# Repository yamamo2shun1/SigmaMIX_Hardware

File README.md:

# SigmaMIX
The SigmaMIX is a DSP/BLE board for Turntablist/Portablist, and it's an Open Source Hardware.

# Firmware/Software Repository
* [SigmaMIX Firmware for SiLabs BGM113](https://github.com/tkrworks/SigmaMIX_Firmware)  
* [SigmaMIX Remote App for Android](https://github.com/tkrworks/SigmaMIX_Remote)

**I made sure to be able to control two ADAU1701 from the BGM113 via I2C on June 7 2017!!!**

## Test Video
[Delay Test](https://www.instagram.com/p/BXrRHsZBKkE/)  
[Effect and Scratch DEMO](https://www.instagram.com/p/BXWzQCQBJe1/)  
[Phono and Line inputs Mix and Fader Cutting Test](https://www.instagram.com/p/BV4aKTPhfiU/)  
[3-Band EQ Test via BLE](https://www.instagram.com/p/BVq-pJHB9hm/)  
[Phono EQ Test](https://www.instagram.com/p/BVVsefTBJXY/)  
[Beat and Sine Tone Test](https://www.instagram.com/p/BVFF-J9hF4o/)  
[First Scratch Test](https://www.instagram.com/p/BUi_Y2OhvBm/)  

## SPEC
* DSP: ANALOG DEVICES SigmaDSP [ADAU1701](http://www.analog.com/jp/products/processors-dsp/sigmadsp-audio-processors/adau1701.html) x2
* BLE: Silicon Labs [BGM113](http://jp.silabs.com/products/wireless/bluetooth/bluetooth-low-energy-modules/bgm113-bluetooth-low-energy-module)
* Audio: RCA Input x4 and RCA Output x8
* Power: ONLY 5-16V input [MIC39101](http://www.microchip.com/wwwproducts/en/MIC39100).
* Size: 112.0mm x 59.5mm

## HARDWARE LICENSE
<br /><span xmlns:dct="http://purl.org/dc/terms/" property="dct:title">SigmaMIX</span> by <span xmlns:cc="http://creativecommons.org/ns#" property="cc:attributionName">Shunichi Yamamoto</span> is licensed under a <a rel="license" href="http://creativecommons.org/licenses/by-sa/4.0/">Creative Commons Attribution-ShareAlike 4.0 International License</a>.

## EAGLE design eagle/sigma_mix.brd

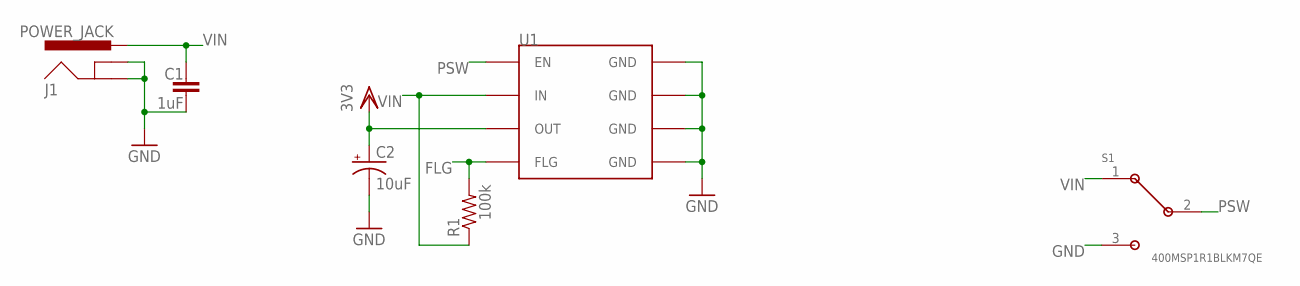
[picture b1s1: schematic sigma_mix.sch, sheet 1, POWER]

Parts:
C1: 1uF; C2012
C2: 10uF; R/2012-12R
J1: POWER_JACK; POWER_JACK_PTH_LOCK
R1: 100k; 0603-RES
S1: 400MSP1R1BLKM7QE
U1: MIC39100; SOIC8

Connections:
FLG: R1.2, U1.4 (FLG)
GND: C1.2, C2.-, J1.GND, J1.GNDBREAK, S1.3, U1.5 (GND), U1.6 (GND), U1.7 (GND), U1.8 (GND); also elsewhere on the board
PSW: S1.2, U1.1 (EN)
VDD: C2.+, U1.3 (OUT); also elsewhere on the board
VIN: C1.1, J1.PWR, R1.1, S1.1, U1.2 (IN)

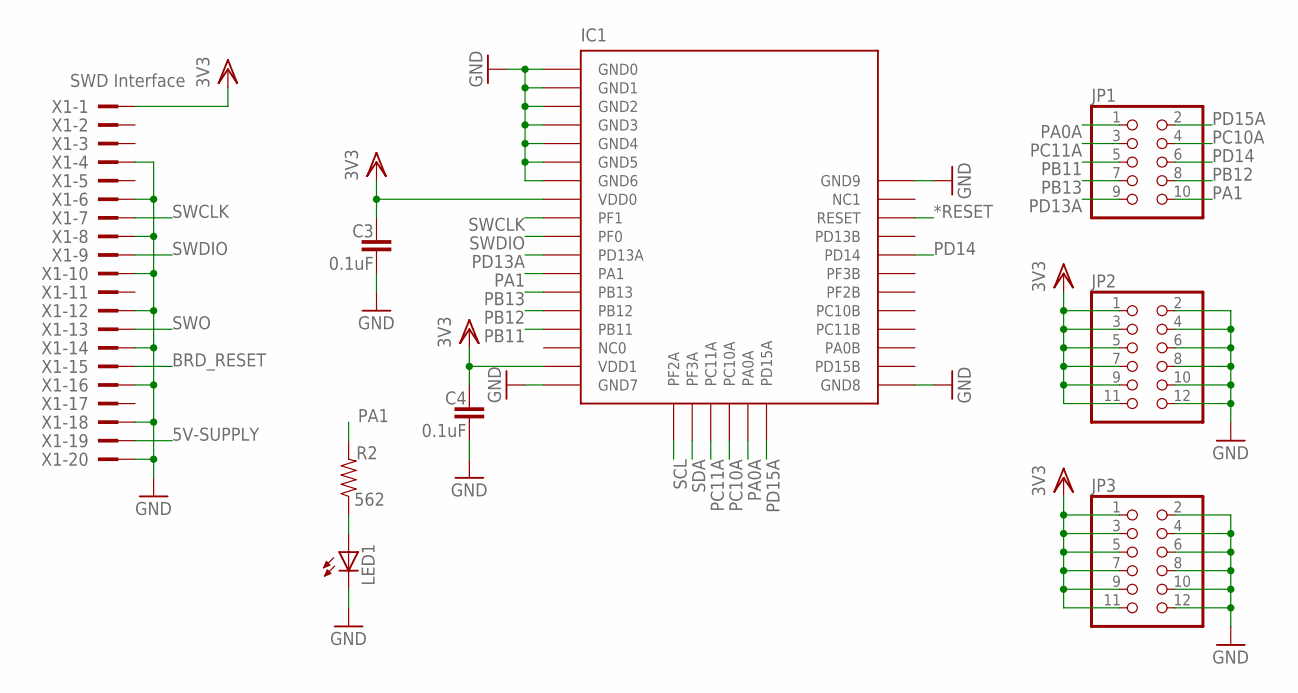
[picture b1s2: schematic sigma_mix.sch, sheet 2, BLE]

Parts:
C3, C4: 0.1uF; C2012
IC1: BGM113; BLE113
JP1: PINHD-2X5; 2X05
JP2, JP3: PINHD-2X6; 2X06
LED1: LEDCHIPLED_1206; CHIPLED_1206
R2: 562; 0603-RES
X1: SWD Interface; PAK100/2500-20

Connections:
5V-SUPPLY: X1.19
*RESET: IC1.P$34 (RESET); also elsewhere on the board
BRD_RESET: X1.15; also elsewhere on the board
GND: C3.2, C4.2, IC1.P$1 (GND0), IC1.P$2 (GND1), IC1.P$3 (GND2), IC1.P$4 (GND3), IC1.P$5 (GND4), IC1.P$6 (GND5), IC1.P$7 (GND6), IC1.P$18 (GND7), IC1.P$25 (GND8), IC1.P$36 (GND9), JP2.2, JP2.4, JP2.6, JP2.8, JP2.10, JP2.12, JP3.2, JP3.4, JP3.6, JP3.8, JP3.10, JP3.12, LED1.C, X1.4, X1.6, X1.8, X1.10, X1.12, X1.14, X1.16, X1.18, X1.20; also elsewhere on the board
unnamed: LED1.A, R2.1
PA0A: IC1.P$23 (PA0A), JP1.1
PA1: IC1.P$12 (PA1), JP1.10, R2.2
PB11: IC1.P$15 (PB11), JP1.5
PB12: IC1.P$14 (PB12), JP1.8
PB13: IC1.P$13 (PB13), JP1.7
PC10A: IC1.P$22 (PC10A), JP1.4
PC11A: IC1.P$21 (PC11A), JP1.3
PD13A: IC1.P$11 (PD13A), JP1.9
PD14: IC1.P$32 (PD14), JP1.6
PD15A: IC1.P$24 (PD15A), JP1.2
SCL: IC1.P$19 (PF2A); also elsewhere on the board
SDA: IC1.P$20 (PF3A); also elsewhere on the board
SWCLK: IC1.P$9 (PF1), X1.7
SWDIO: IC1.P$10 (PF0), X1.9
SWO: X1.13
VDD: C3.1, C4.1, IC1.P$8 (VDD0), IC1.P$17 (VDD1), JP2.1, JP2.3, JP2.5, JP2.7, JP2.9, JP2.11, JP3.1, JP3.3, JP3.5, JP3.7, JP3.9, JP3.11, X1.1; also elsewhere on the board

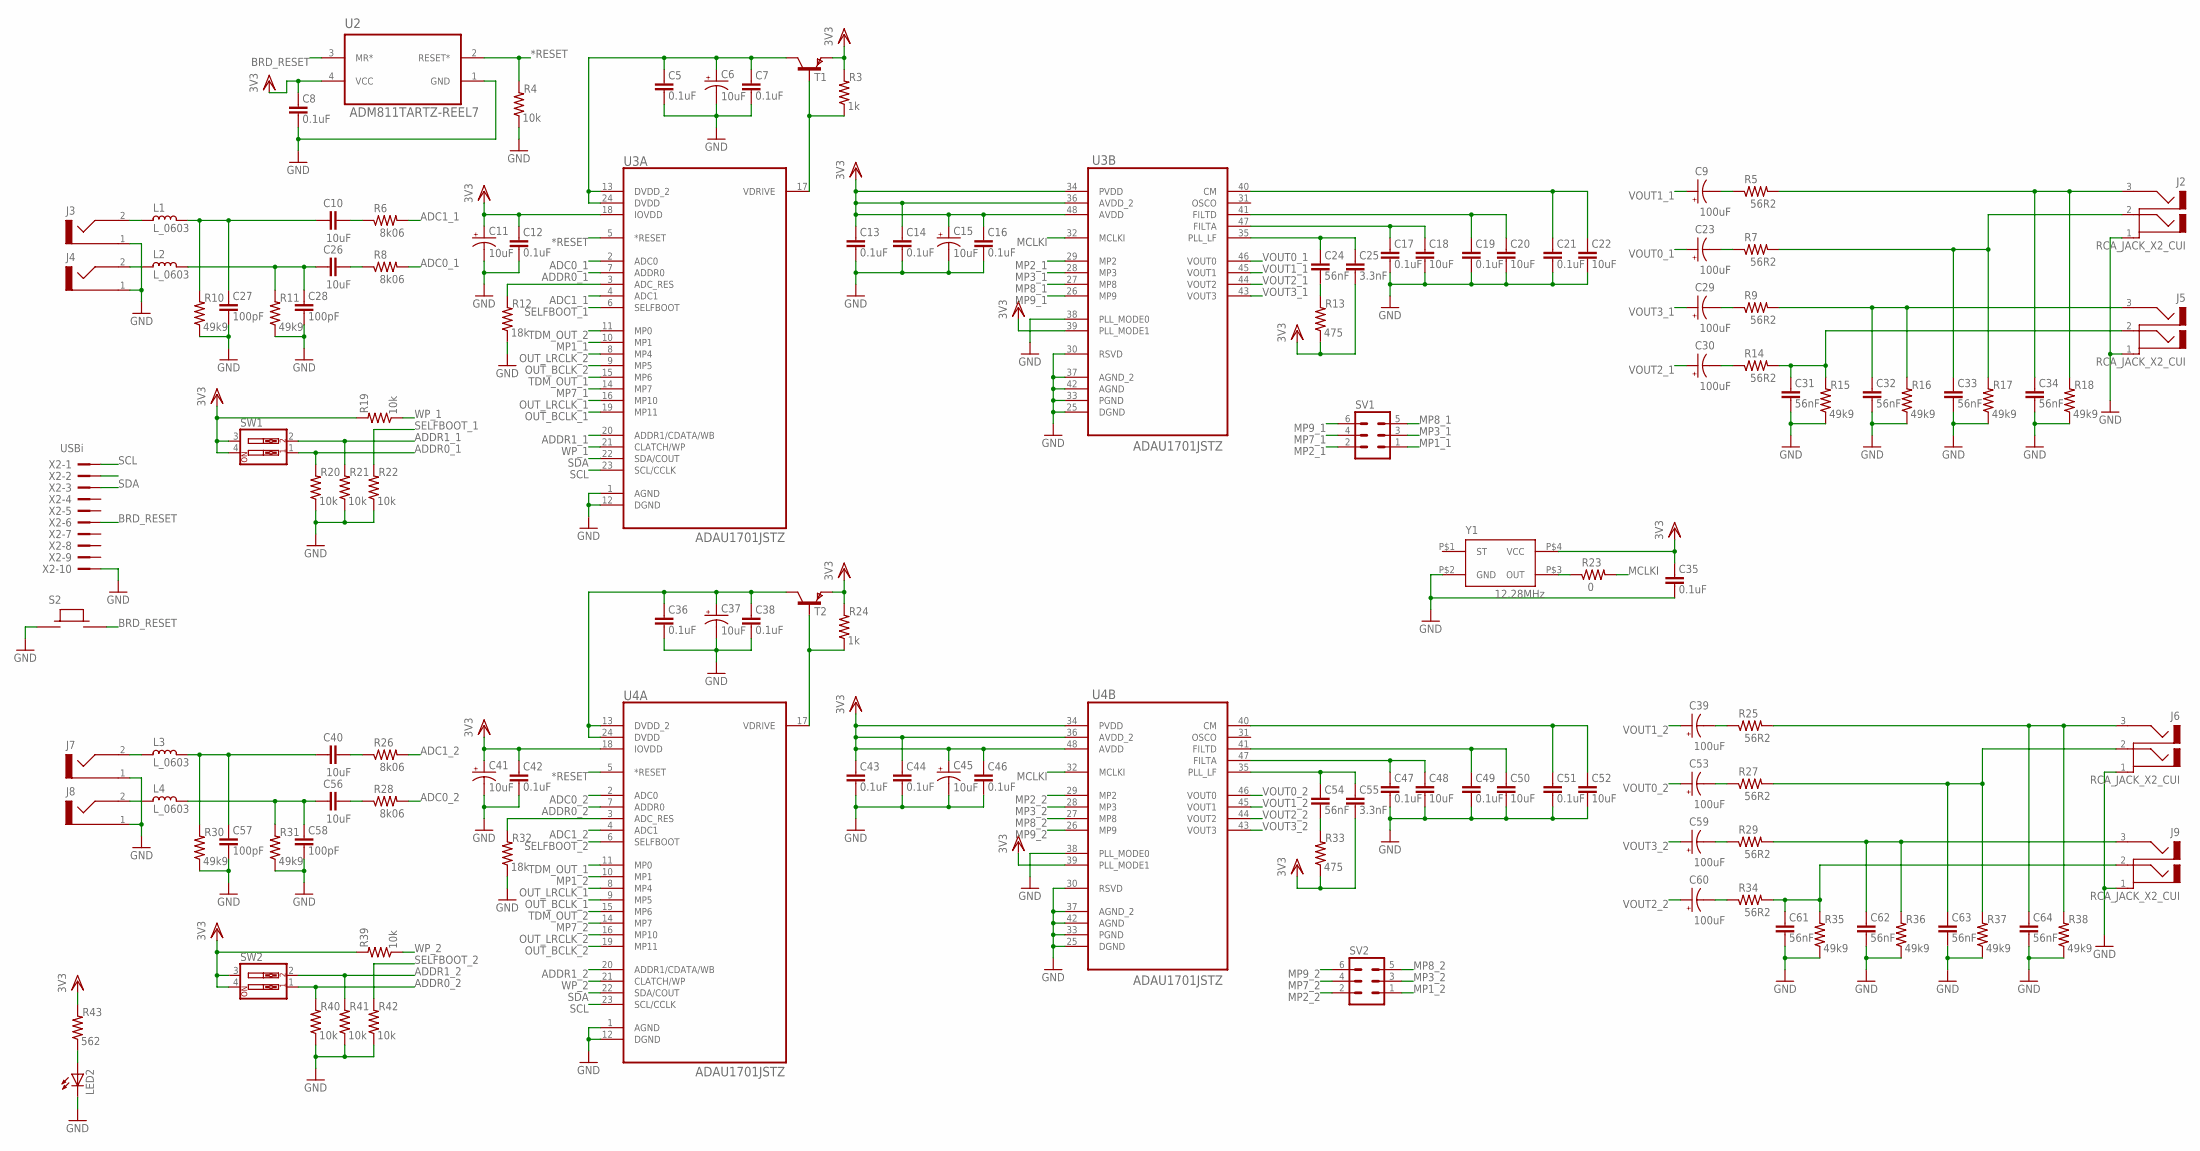
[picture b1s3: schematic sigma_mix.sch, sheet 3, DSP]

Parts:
C5, C7, C8, C12, C13, C14, C16, C17, C19, C21, C35, C36, C38, C42, C43, C44, C46, C47, C49, C51: 0.1uF; C2012
C6, C11, C15, C37, C41, C45: 10uF; R/2012-12R
C9, C23, C29, C30, C39, C53, C59, C60: 100uF; B/3528-21R
C10, C18, C20, C22, C26, C40, C48, C50, C52, C56: 10uF; C2012
C24, C31, C32, C33, C34, C54, C61, C62, C63, C64: 56nF; C2012
C25, C55: 3.3nF; C2012
C27, C28, C57, C58: 100pF; C2012
J2, J5, J6, J9: RCA_JACK_X2_CUI
J3, J4, J7, J8: RCA_JACK_CUI
L1, L2, L3, L4: L_0603; L0603
LED2: LEDCHIPLED_1206; CHIPLED_1206
R3, R24: 1k; 0603-RES
R4, R19, R20, R21, R22, R39, R40, R41, R42: 10k; 0603-RES
R5, R7, R9, R14, R25, R27, R29, R34: 56R2; 0603-RES
R6, R8, R26, R28: 8k06; 0603-RES
R10, R11, R15, R16, R17, R18, R30, R31, R35, R36, R37, R38: 49k9; 0603-RES
R12, R32: 18k; 0603-RES
R13, R33: 475; 0603-RES
R23: 0; 0603-RES
R43: 562; 0603-RES
S2: OMRON_B3M
SV1, SV2: MA03-2
SW1, SW2: SW_DIP-2; EDG-02
T1, T2: PNPSOT23; SOT-23
U2: ADM811TARTZ-REEL7; SOT143P290X130-4N
U3, U4: ADAU1701JSTZ; QFP50P900X900X160-48N
X2: USBi; PAK100/2500-10
Y1: 12.28MHz; SG-210

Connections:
*RESET: R4.2, U2.2 (RESET*), U3.5 (*RESET), U4.5 (*RESET); also elsewhere on the board
ADC0_1: R8.2, U3.2 (ADC0)
ADC0_2: R28.2, U4.2 (ADC0)
ADC1_1: R6.2, U3.4 (ADC1)
ADC1_2: R26.2, U4.4 (ADC1)
ADDR0_1: R20.2, SW1.1, U3.7 (ADDR0)
ADDR0_2: R40.2, SW2.1, U4.7 (ADDR0)
ADDR1_1: R21.2, SW1.2, U3.20 (ADDR1/CDATA/WB)
ADDR1_2: R41.2, SW2.2, U4.20 (ADDR1/CDATA/WB)
BRD_RESET: S2.P$2, U2.3 (MR*), X2.6; also elsewhere on the board
DVDD: C5.1, C6.+, C7.1, T1.1 (C), U3.13 (DVDD_2), U3.24 (DVDD)
GND: C5.2, C6.-, C7.2, C8.2, C11.-, C12.2, C13.2, C14.2, C15.-, C16.2, C17.2, C18.2, C19.2, C20.2, C21.2, C22.2, C27.2, C28.2, C31.2, C32.2, C33.2, C34.2, C35.2, C36.2, C37.-, C38.2, C41.-, C42.2, C43.2, C44.2, C45.-, C46.2, C47.2, C48.2, C49.2, C50.2, C51.2, C52.2, C57.2, C58.2, C61.2, C62.2, C63.2, C64.2, J2.1, J3.1, J4.1, J5.1, J6.1, J7.1, J8.1, J9.1, LED2.C, R4.1, R10.1, R11.1, R12.1, R15.1, R16.1, R17.1, R18.1, R20.1, R21.1, R22.1, R30.1, R31.1, R32.1, R35.1, R36.1, R37.1, R38.1, R40.1, R41.1, R42.1, S2.P$1, U2.1 (GND), U3.1 (AGND), U3.12 (DGND), U3.25 (DGND), U3.30 (RSVD), U3.33 (PGND), U3.37 (AGND_2), U3.38 (PLL_MODE0), U3.42 (AGND), U4.1 (AGND), U4.12 (DGND), U4.25 (DGND), U4.30 (RSVD), U4.33 (PGND), U4.37 (AGND_2), U4.38 (PLL_MODE0), U4.42 (AGND), X2.10, Y1.P$2 (GND); also elsewhere on the board
MCLKI: R23.2, U3.32 (MCLKI), U4.32 (MCLKI)
MP1_1: SV1.1, U3.10 (MP1)
MP1_2: SV2.1, U4.10 (MP1)
MP2_1: SV1.2, U3.29 (MP2)
MP2_2: SV2.2, U4.29 (MP2)
MP3_1: SV1.3, U3.28 (MP3)
MP3_2: SV2.3, U4.28 (MP3)
MP7_1: SV1.4, U3.14 (MP7)
MP7_2: SV2.4, U4.14 (MP7)
MP8_1: SV1.5, U3.27 (MP8)
MP8_2: SV2.5, U4.27 (MP8)
MP9_1: SV1.6, U3.26 (MP9)
MP9_2: SV2.6, U4.26 (MP9)
unnamed: R3.1, T1.3 (B), U3.17 (VDRIVE)
unnamed: C24.2, R13.2
unnamed: C24.1, C25.1, U3.35 (PLL_LF)
unnamed: C17.1, C18.1, U3.47 (FILTA)
unnamed: R23.1, Y1.P$3 (OUT)
unnamed: C19.1, C20.1, U3.41 (FILTD)
unnamed: C21.1, C22.1, U3.40 (CM)
unnamed: R12.2, U3.3 (ADC_RES)
unnamed: LED2.A, R43.1
unnamed: C10.2, C27.1, L1.1, R10.2
unnamed: C10.1, R6.1
unnamed: C26.2, C28.1, L2.1, R11.2
unnamed: C26.1, R8.1
unnamed: C9.-, R5.1
unnamed: J3.2, L1.2
unnamed: C23.-, R7.1
unnamed: C29.-, R9.1
unnamed: C30.-, R14.1
unnamed: C31.1, J5.2, R14.2, R15.2
unnamed: C32.1, J5.3, R9.2, R16.2
unnamed: C33.1, J2.2, R7.2, R17.2
unnamed: C34.1, J2.3, R5.2, R18.2
unnamed: J4.2, L2.2
unnamed: R24.1, T2.3 (B), U4.17 (VDRIVE)
unnamed: C36.1, C37.+, C38.1, T2.1 (C), U4.13 (DVDD_2), U4.24 (DVDD)
unnamed: C54.2, R33.2
unnamed: C54.1, C55.1, U4.35 (PLL_LF)
unnamed: C47.1, C48.1, U4.47 (FILTA)
unnamed: C49.1, C50.1, U4.41 (FILTD)
unnamed: C51.1, C52.1, U4.40 (CM)
unnamed: R32.2, U4.3 (ADC_RES)
unnamed: C40.2, C57.1, L3.1, R30.2
unnamed: C40.1, R26.1
unnamed: C56.2, C58.1, L4.1, R31.2
unnamed: C56.1, R28.1
unnamed: C39.-, R25.1
unnamed: C53.-, R27.1
unnamed: C59.-, R29.1
unnamed: C60.-, R34.1
unnamed: C61.1, J9.2, R34.2, R35.2
unnamed: C62.1, J9.3, R29.2, R36.2
unnamed: C63.1, J6.2, R27.2, R37.2
unnamed: C64.1, J6.3, R25.2, R38.2
unnamed: J7.2, L3.2
unnamed: J8.2, L4.2
OUT_BCLK_1: U3.19 (MP11), U4.9 (MP5)
OUT_BCLK_2: U3.9 (MP5), U4.19 (MP11)
OUT_LRCLK_1: U3.16 (MP10), U4.8 (MP4)
OUT_LRCLK_2: U3.8 (MP4), U4.16 (MP10)
SCL: U3.23 (SCL/CCLK), U4.23 (SCL/CCLK), X2.1; also elsewhere on the board
SDA: U3.22 (SDA/COUT), U4.22 (SDA/COUT), X2.3; also elsewhere on the board
SELFBOOT_1: R22.2, U3.6 (SELFBOOT)
SELFBOOT_2: R42.2, U4.6 (SELFBOOT)
TDM_OUT_1: U3.15 (MP6), U4.11 (MP0)
TDM_OUT_2: U3.11 (MP0), U4.15 (MP6)
VDD: C8.1, C11.+, C12.1, C13.1, C14.1, C15.+, C16.1, C25.2, C35.1, C41.+, C42.1, C43.1, C44.1, C45.+, C46.1, C55.2, R3.2, R13.1, R19.2, R24.2, R33.1, R39.2, R43.2, SW1.3, SW1.4, SW2.3, SW2.4, T1.2 (E), T2.2 (E), U2.4 (VCC), U3.18 (IOVDD), U3.34 (PVDD), U3.36 (AVDD_2), U3.39 (PLL_MODE1), U3.48 (AVDD), U4.18 (IOVDD), U4.34 (PVDD), U4.36 (AVDD_2), U4.39 (PLL_MODE1), U4.48 (AVDD), Y1.P$4 (VCC); also elsewhere on the board
VOUT0_1: C23.+, U3.46 (VOUT0)
VOUT0_2: C53.+, U4.46 (VOUT0)
VOUT1_1: C9.+, U3.45 (VOUT1)
VOUT1_2: C39.+, U4.45 (VOUT1)
VOUT2_1: C30.+, U3.44 (VOUT2)
VOUT2_2: C60.+, U4.44 (VOUT2)
VOUT3_1: C29.+, U3.43 (VOUT3)
VOUT3_2: C59.+, U4.43 (VOUT3)
WP_1: R19.1, U3.21 (CLATCH/WP)
WP_2: R39.1, U4.21 (CLATCH/WP)

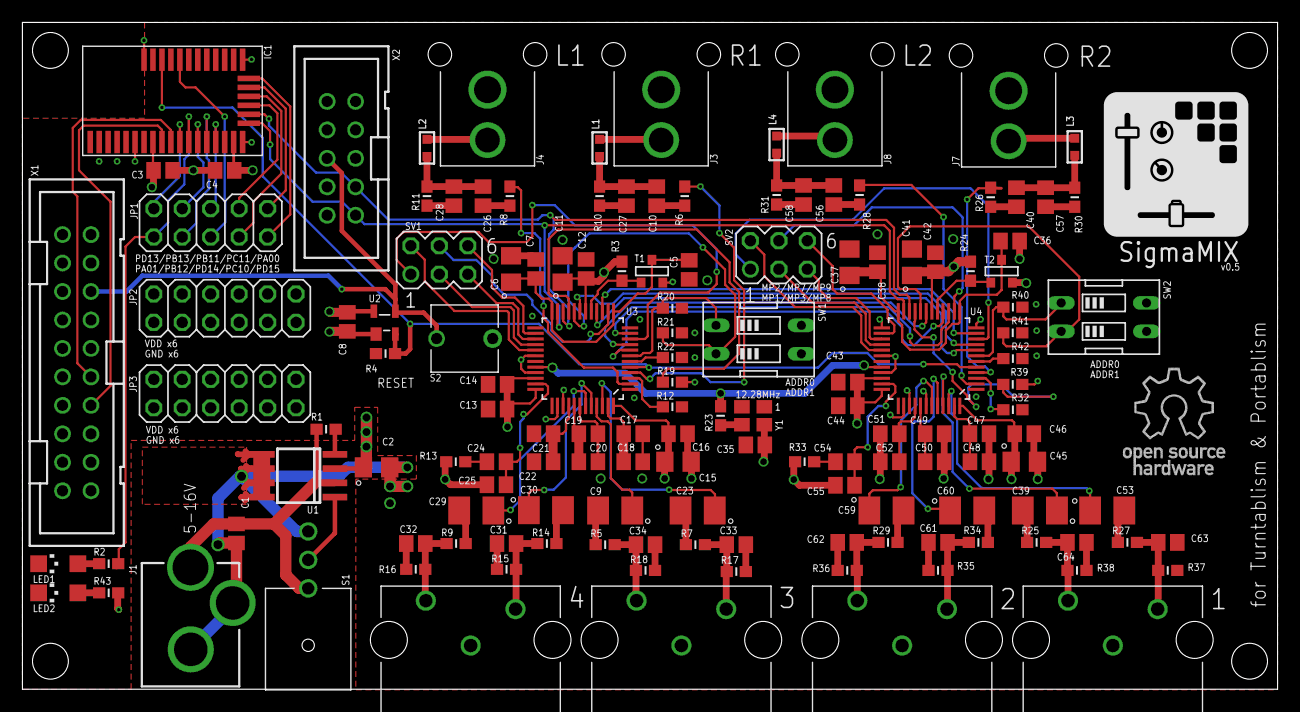
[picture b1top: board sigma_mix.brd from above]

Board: 4 copper layers, 112.0 x 59.5 mm, 141 parts (0 on the bottom side), 107 nets.

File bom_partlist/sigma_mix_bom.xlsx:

Part | Value | Package | Description | Digikey
C1 | 1uF | 2012 | Multilayer Ceramic Capacitor | 490-1691-1-ND
C2 | 10uF | 2012 | Tantalum Capacitor | 478-8115-1-ND
C3 | 0.1uF | 2012 | Multilayer Ceramic Capacitor | 490-1683-6-ND
C4 | 0.1uF | 2012 | Multilayer Ceramic Capacitor | 490-1683-6-ND
C5 | 0.1uF | 2012 | Multilayer Ceramic Capacitor | 490-1683-6-ND
C6 | 10uF | 2012 | Tantalum Capacitor | 478-8115-1-ND
C7 | 0.1uF | 2012 | Multilayer Ceramic Capacitor | 490-1683-6-ND
C8 | 0.1uF | 2012 | Multilayer Ceramic Capacitor | 490-1683-6-ND
C9 | 100uF | 3528 | Tantalum Capacitor | 718-1313-1-ND
C10 | 10uF | 2012 | Multilayer Ceramic Capacitor | 490-3905-1-ND
C11 | 10uF | 2012 | Tantalum Capacitor | 478-8115-1-ND
C12 | 0.1uF | 2012 | Multilayer Ceramic Capacitor | 490-1683-6-ND
C13 | 0.1uF | 2012 | Multilayer Ceramic Capacitor | 490-1683-6-ND
C14 | 0.1uF | 2012 | Multilayer Ceramic Capacitor | 490-1683-6-ND
C15 | 10uF | 2012 | Tantalum Capacitor | 478-8115-1-ND
C16 | 0.1uF | 2012 | Multilayer Ceramic Capacitor | 490-1683-6-ND
C17 | 0.1uF | 2012 | Multilayer Ceramic Capacitor | 490-1683-6-ND
C18 | 10uF | 2012 | Multilayer Ceramic Capacitor | 490-3905-1-ND
C19 | 0.1uF | 2012 | Multilayer Ceramic Capacitor | 490-1683-6-ND
C20 | 10uF | 2012 | Multilayer Ceramic Capacitor | 490-3905-1-ND
C21 | 0.1uF | 2012 | Multilayer Ceramic Capacitor | 490-1683-6-ND
C22 | 10uF | 2012 | Multilayer Ceramic Capacitor | 490-3905-1-ND
C23 | 100uF | 3528 | Tantalum Capacitor | 718-1313-1-ND
C24 | 56nF | 2012 | Multilayer Ceramic Capacitor | 490-1662-1-ND
C25 | 3.3nF | 2012 | Multilayer Ceramic Capacitor | 399-1153-1-ND
C26 | 10uF | 2012 | Multilayer Ceramic Capacitor | 490-3905-1-ND
C27 | 100pF | 2012 | Multilayer Ceramic Capacitor | 490-1615-1-ND
C28 | 100pF | 2012 | Multilayer Ceramic Capacitor | 490-1615-1-ND
C29 | 100uF | 3528 | Tantalum Capacitor | 718-1313-1-ND
C30 | 100uF | 3528 | Tantalum Capacitor | 718-1313-1-ND
C31 | 56nF | 2012 | Multilayer Ceramic Capacitor | 490-1662-1-ND
C32 | 56nF | 2012 | Multilayer Ceramic Capacitor | 490-1662-1-ND
C33 | 56nF | 2012 | Multilayer Ceramic Capacitor | 490-1662-1-ND
C34 | 56nF | 2012 | Multilayer Ceramic Capacitor | 490-1662-1-ND
C35 | 0.1uF | 2012 | Multilayer Ceramic Capacitor | 490-1683-6-ND
C36 | 0.1uF | 2012 | Multilayer Ceramic Capacitor | 490-1683-6-ND
C37 | 10uF | 2012 | Tantalum Capacitor | 478-8115-1-ND
C38 | 0.1uF | 2012 | Multilayer Ceramic Capacitor | 490-1683-6-ND
C39 | 100uF | 3528 | Tantalum Capacitor | 718-1313-1-ND
C40 | 10uF | 2012 | Multilayer Ceramic Capacitor | 490-3905-1-ND
C41 | 10uF | 2012 | Tantalum Capacitor | 478-8115-1-ND
C42 | 0.1uF | 2012 | Multilayer Ceramic Capacitor | 490-1683-6-ND
C43 | 0.1uF | 2012 | Multilayer Ceramic Capacitor | 490-1683-6-ND
C44 | 0.1uF | 2012 | Multilayer Ceramic Capacitor | 490-1683-6-ND
C45 | 10uF | 2012 | Tantalum Capacitor | 478-8115-1-ND
C46 | 0.1uF | 2012 | Multilayer Ceramic Capacitor | 490-1683-6-ND
C47 | 0.1uF | 2012 | Multilayer Ceramic Capacitor | 490-1683-6-ND
C48 | 10uF | 2012 | Multilayer Ceramic Capacitor | 490-3905-1-ND
C49 | 0.1uF | 2012 | Multilayer Ceramic Capacitor | 490-1683-6-ND
C50 | 10uF | 2012 | Multilayer Ceramic Capacitor | 490-3905-1-ND
C51 | 0.1uF | 2012 | Multilayer Ceramic Capacitor | 490-1683-6-ND
C52 | 10uF | 2012 | Multilayer Ceramic Capacitor | 490-3905-1-ND
C53 | 100uF | 3528 | Tantalum Capacitor | 718-1313-1-ND
C54 | 56nF | 2012 | Multilayer Ceramic Capacitor | 490-1662-1-ND
C55 | 3.3nF | 2012 | Multilayer Ceramic Capacitor | 399-1153-1-ND
C56 | 10uF | 2012 | Multilayer Ceramic Capacitor | 490-3905-1-ND
C57 | 100pF | 2012 | Multilayer Ceramic Capacitor | 490-1615-1-ND
C58 | 100pF | 2012 | Multilayer Ceramic Capacitor | 490-1615-1-ND
C59 | 100uF | 3528 | Tantalum Capacitor | 718-1313-1-ND
C60 | 100uF | 3528 | Tantalum Capacitor | 718-1313-1-ND
C61 | 56nF | 2012 | Multilayer Ceramic Capacitor | 490-1662-1-ND
C62 | 56nF | 2012 | Multilayer Ceramic Capacitor | 490-1662-1-ND
C63 | 56nF | 2012 | Multilayer Ceramic Capacitor | 490-1662-1-ND
C64 | 56nF | 2012 | Multilayer Ceramic Capacitor | 490-1662-1-ND
IC1 | BGM113 | LGA Module | Bluetooth Module | 336-3817-1-ND
J1 | DC_JACK | Through Hole | Power Connector |  | 未実装ミジッソウ
J2 | RCA2_JACK | Through Hole | Audio Connector | CP-1435-ND | 未実装ミジッソウ
J3 | RCA_JACK | Through Hole | Audio Connector | CP-1419-ND | 未実装ミジッソウ
J4 | RCA_JACK | Through Hole | Audio Connector | CP-1420-ND | 未実装ミジッソウ
J5 | RCA2_JACK | Through Hole | Audio Connector | CP-1435-ND | 未実装ミジッソウ
J6 | RCA2_JACK | Through Hole | Audio Connector | CP-1435-ND | 未実装ミジッソウ
J7 | RCA_JACK | Through Hole | Audio Connector | CP-1419-ND | 未実装ミジッソウ
J8 | RCA_JACK | Through Hole | Audio Connector | CP-1420-ND | 未実装ミジッソウ
J9 | RCA2_JACK | Through Hole | Audio Connector | CP-1435-ND | 未実装ミジッソウ
JP1 | 2x5 | Through Hole | Pin Header |  | 未実装ミジッソウ
JP2 | 2x6 | Through Hole | Pin Header |  | 未実装ミジッソウ
JP3 | 2x6 | Through Hole | Pin Header |  | 未実装ミジッソウ
L1 | 600ohm@100MHz | 1608 | Ferrite Beads | 490-14396-1-ND
L2 | 600ohm@100MHz | 1608 | Ferrite Beads | 490-14396-1-ND
L3 | 600ohm@100MHz | 1608 | Ferrite Beads | 490-14396-1-ND
L4 | 600ohm@100MHz | 1608 | Ferrite Beads | 490-14396-1-ND
LED1 | GREEN | 3216 | LED | 67-1002-1-ND
LED2 | RED | 3216 | LED | 67-1003-1-ND
R1 | 100k | 1608 | Resistor | P100KHCT-ND
R2 | 562 | 1608 | Resistor | P562HCT-ND
R3 | 1k | 1608 | Resistor | P1.00KHCT-ND
R4 | 10k | 1608 | Resistor | P10.0KHCT-ND
R5 | 56R2 | 1608 | Resistor | P56.2HCT-ND
R6 | 8k06 | 1608 | Resistor | P8.06KHCT-ND
R7 | 56R2 | 1608 | Resistor | P56.2HCT-ND
R8 | 8k06 | 1608 | Resistor | P8.06KHCT-ND
R9 | 56R2 | 1608 | Resistor | P56.2HCT-ND
R10 | 49k9 | 1608 | Resistor | P49.9KHCT-ND
R11 | 49k9 | 1608 | Resistor | P49.9KHCT-ND
R12 | 18k | 1608 | Resistor | P18.0KHCT-ND
R13 | 475 | 1608 | Resistor | P475HCT-ND
R14 | 56R2 | 1608 | Resistor | P56.2HCT-ND
R15 | 49k9 | 1608 | Resistor | P49.9KHCT-ND
R16 | 49k9 | 1608 | Resistor | P49.9KHCT-ND
R17 | 49k9 | 1608 | Resistor | P49.9KHCT-ND
R18 | 49k9 | 1608 | Resistor | P49.9KHCT-ND
R19 | 10k | 1608 | Resistor | P10.0KHCT-ND
R20 | 10k | 1608 | Resistor | P10.0KHCT-ND
R21 | 10k | 1608 | Resistor | P10.0KHCT-ND
R22 | 10k | 1608 | Resistor | P10.0KHCT-ND
R23 | 0 | 1608 | Resistor | P0.0ACT-ND
R24 | 1k | 1608 | Resistor | P1.00KHCT-ND
R25 | 56R2 | 1608 | Resistor | P56.2HCT-ND
R26 | 8k06 | 1608 | Resistor | P8.06KHCT-ND
R27 | 56R2 | 1608 | Resistor | P56.2HCT-ND
R28 | 8k06 | 1608 | Resistor | P8.06KHCT-ND
R29 | 56R2 | 1608 | Resistor | P56.2HCT-ND
R30 | 49k9 | 1608 | Resistor | P49.9KHCT-ND
R31 | 49k9 | 1608 | Resistor | P49.9KHCT-ND
R32 | 18k | 1608 | Resistor | P18.0KHCT-ND
R33 | 475 | 1608 | Resistor | P475HCT-ND
R34 | 56R2 | 1608 | Resistor | P56.2HCT-ND
R35 | 49k9 | 1608 | Resistor | P49.9KHCT-ND
R36 | 49k9 | 1608 | Resistor | P49.9KHCT-ND
R37 | 49k9 | 1608 | Resistor | P49.9KHCT-ND
R38 | 49k9 | 1608 | Resistor | P49.9KHCT-ND
R39 | 10k | 1608 | Resistor | P10.0KHCT-ND
R40 | 10k | 1608 | Resistor | P10.0KHCT-ND
R41 | 10k | 1608 | Resistor | P10.0KHCT-ND
R42 | 10k | 1608 | Resistor | P10.0KHCT-ND
R43 | 562 | 1608 | Resistor | P562HCT-ND
S1 | ROCKER SW | Through Hole | Switch | EG4328-ND | 未実装ミジッソウ
S2 | TACTILE SW | Through Hole | Switch | EG4328-ND | 未実装ミジッソウ
SV1 | 2x3 | Through Hole | Pin Header |  | 未実装ミジッソウ
SV2 | 2x3 | Through Hole | Pin Header |  | 未実装ミジッソウ
SW1 | DIP SW | Through Hole | Switch | SW1194-ND | 未実装ミジッソウ
SW2 | DIP SW | Through Hole | Switch | SW1194-ND | 未実装ミジッソウ
T1 | PNP | SOT-23 | Transistor | ZXTP25040DFHCT-ND
T2 | PNP | SOT-23 | Transistor | ZXTP25040DFHCT-ND
U1 | MIC39101 | SOIC8 | Power Regulator IC | 576-1782-5-ND
U2 | ADM811 | SOT-143 | Reset IC | ADM811TARTZ-REEL7CT-ND
U3 | ADAU1701 | LQFP48 | DSP IC | ADAU1701JSTZ-RLCT-ND
U4 | ADAU1701 | LQFP48 | DSP IC | ADAU1701JSTZ-RLCT-ND
X1 | SWD Interface | Through Hole | Connector | MHC20K-ND | 未実装ミジッソウ
X2 | USBi | Through Hole | Connector | MHC10K-ND | 未実装ミジッソウ
Y1 | 12.28MHz | SMD | Crystal Oscillator | 535-10902-1-ND

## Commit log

2017-04-19 Add eagle files.
2017-04-19 Add gerber files.
2017-04-19 add schematic pdfs.
2017-04-19 add board pdf.
2017-04-19 Create README.
2017-04-19 Add comment.
2017-04-19 Add license.
2017-04-19 Update README.
2017-04-19 Add part list.
2017-04-19 add png for README.
2017-04-19 Revert "add png for README."
    This reverts commit 8ac4937f4ba61a312aa80bb4c972a10f83b12d2a.
2017-04-19 Add board image.
2017-04-26 Add part No. and Change xtal.
2017-04-26 Add BOM and update part list.
2017-04-26 Move metalmask data.
2017-04-26 Add mount data.
2017-04-26 Update gerver.
2017-05-07 Release ver0.2.
    Fixed some bugs of issue.
2017-05-07 Update PNG.
2017-05-15 Update brd image.
2017-05-15 Fixed some silk positions.
2017-05-15 Release ver0.3.
    Fixed the issue #11, #12, #13.
    Fixed some silk positions.
2017-05-15 Release ver0.3.
2017-05-15 Fixed the IC part number.
2017-05-15 Add the picture of ver0.2 PCB board.
2017-05-15 Add the PCB picture.
2017-06-08 Reseale ver 0.4.
    Fxed the issues #14, #15, #16 and #18.
2017-06-08 Update ver 0.4.
2017-06-10 First commit.
2017-06-15 Append a new test movie link.
2017-06-22 Move the firmware directory to other repository.
2017-06-22 Add the AutoCAD LT 2018 DWG and PDF.
2017-06-23 Update README
    Add the repositories of firmware and software.
    Add the test vid link.
2017-06-29 Update to v0.5.
2017-08-03 Update the BOM and parts list.
2017-08-03 Revert "Update the BOM and parts list."
    This reverts commit 2f607d859bf7c325c92fad7b5bdf895f4607e224.
2017-08-03 Change the jig's height.
2017-08-03 Update.
2017-08-03 Update PCB image.

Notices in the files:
parts and their libraries:
SparkFun: Licensing: CC v3.0 Share-Alike You are welcome to use this library for commercial purposes.
rc-master-smd: Copyright (C) 2007, Bob Starr
